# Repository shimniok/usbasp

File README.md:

# Introduction

This is an implementation of Fischl's usbasp

USBasp is a USB in-circuit programmer for Atmel AVR controllers consisting
of an ATMega88 or ATMega8 and a few of passive components.

The programmer uses a firmware-only USB driver, no special USB controller
is needed.

## Features

- Works under multiple platforms. Linux, Mac OS X and Windows are tested.
- No special controllers or smd components are needed.
- Programming speed is up to 5kBytes/sec.
- SCK option to support targets with low clock speed (< 1,5MHz).
- Planned: serial interface to target (e.g. for debugging).

# LICENSE

## Electronics

The circuit design is based on Fischl's and is distributed under the terms and conditions of the
MIT license (see ```electronics/LICENSE```)

# LIMITATIONS

## Hardware

This package includes a circuit diagram. This circuit can only be used for
programming 5V target systems. For other systems a level converter is needed.

# FIRMWARE

See http://www.fischl.de/usbasp/ for details on firmware: license, flashing, installation, etc.

Excerpted from Readme.txt, originally:
2011-05-28 Thomas Fischl <tfischl@gmx.de>
http://www.fischl.de

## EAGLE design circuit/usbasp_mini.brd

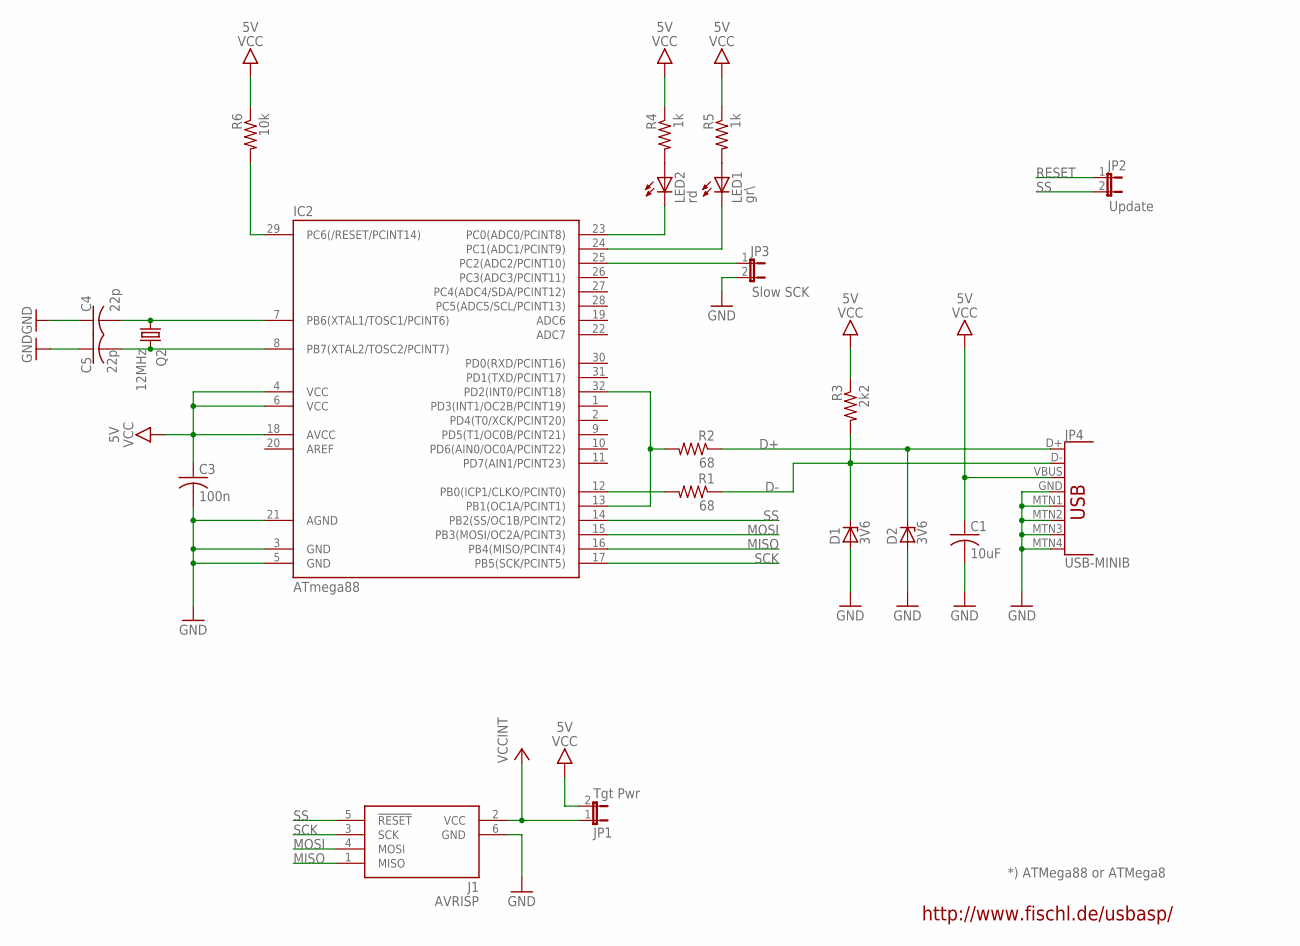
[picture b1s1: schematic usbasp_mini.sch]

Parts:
C1: 10uF; 1206
C3: 100n; 0603
C4, C5: 22p; 0603
D1, D2: 3V6; SMB
IC2: ATmega88; TQFP32-08
J1: AVRISP; CON6P2R
JP1: Tgt Pwr; JP1
JP2: Update; JP1
JP3: Slow SCK; JP1
JP4: USB-MINIB
LED1: gr\; CHIPLED_0603
LED2: rd; CHIPLED_0603
Q2: 12MHz; NDK_2PAD_5X3
R1, R2: 68; 0603
R3: 2k2; 0603
R4, R5: 1k; 0603
R6: 10k; 0603

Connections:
D+: D2.C, JP4.D+, R2.1
D-: D1.C, JP4.D-, R1.1, R3.2
GND: C1.2 (-), C3.2 (-), C4.1 (+), C5.1 (+), D1.A, D2.A, IC2.3 (GND), IC2.5 (GND), IC2.21 (AGND), J1.6 (GND), JP3.2, JP4.GND, JP4.MTN1 (SHIELD1), JP4.MTN2 (SHIELD2), JP4.MTN3 (SHIELD3), JP4.MTN4 (SHIELD4)
MISO: IC2.16 (PB4(MISO/PCINT4)), J1.1 (MISO)
MOSI: IC2.15 (PB3(MOSI/OC2A/PCINT3)), J1.4 (MOSI)
unnamed: IC2.13 (PB1(OC1A/PCINT1)), IC2.32 (PD2(INT0/PCINT18)), R2.2
unnamed: LED2.A, R4.2
unnamed: IC2.12 (PB0(ICP1/CLKO/PCINT0)), R1.2
unnamed: C4.2 (-), IC2.7 (PB6(XTAL1/TOSC1/PCINT6)), Q2.P$1 (1)
unnamed: C5.2 (-), IC2.8 (PB7(XTAL2/TOSC2/PCINT7)), Q2.P$2 (2)
unnamed: LED1.A, R5.2
PC0: IC2.23 (PC0(ADC0/PCINT8)), LED2.C
PC1: IC2.24 (PC1(ADC1/PCINT9)), LED1.C
PC2: IC2.25 (PC2(ADC2/PCINT10)), JP3.1
RESET: IC2.29 (PC6(/RESET/PCINT14)), JP2.1, R6.2
SCK: IC2.17 (PB5(SCK/PCINT5)), J1.3 (SCK)
SS: IC2.14 (PB2(SS/OC1B/PCINT2)), J1.5 (!RESET), JP2.2
VCC: C1.1 (+), C3.1 (+), IC2.4 (VCC), IC2.6 (VCC), IC2.18 (AVCC), JP1.2, JP4.VBUS, R3.1, R4.1, R5.1, R6.1
VCCINT: J1.2 (VCC), JP1.1

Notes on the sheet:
http://www.fischl.de/usbasp/
*) ATMega88 or ATMega8

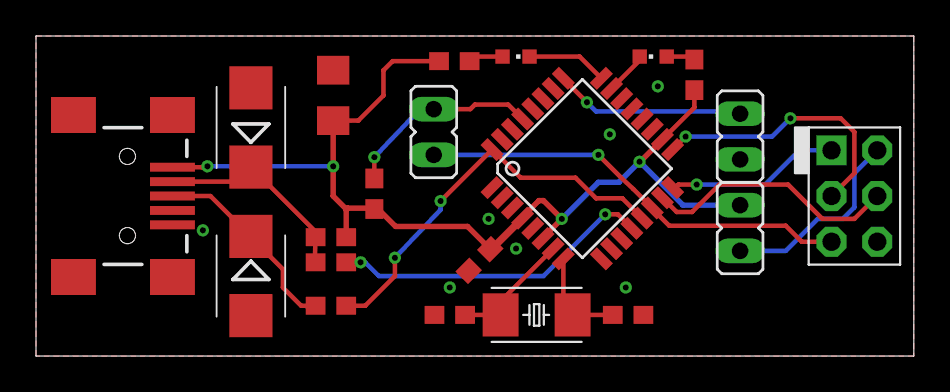
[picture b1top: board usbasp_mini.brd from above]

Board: 2 copper layers, 48.8 x 17.8 mm, 21 parts (0 on the bottom side), 19 nets.

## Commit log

2017-06-14 Create LICENSE
2017-06-14 initial versions
